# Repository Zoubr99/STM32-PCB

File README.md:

# STM32-PCB
 This Repo contains the KiCad 8.0 Files for an STM32-BLE Dev Board

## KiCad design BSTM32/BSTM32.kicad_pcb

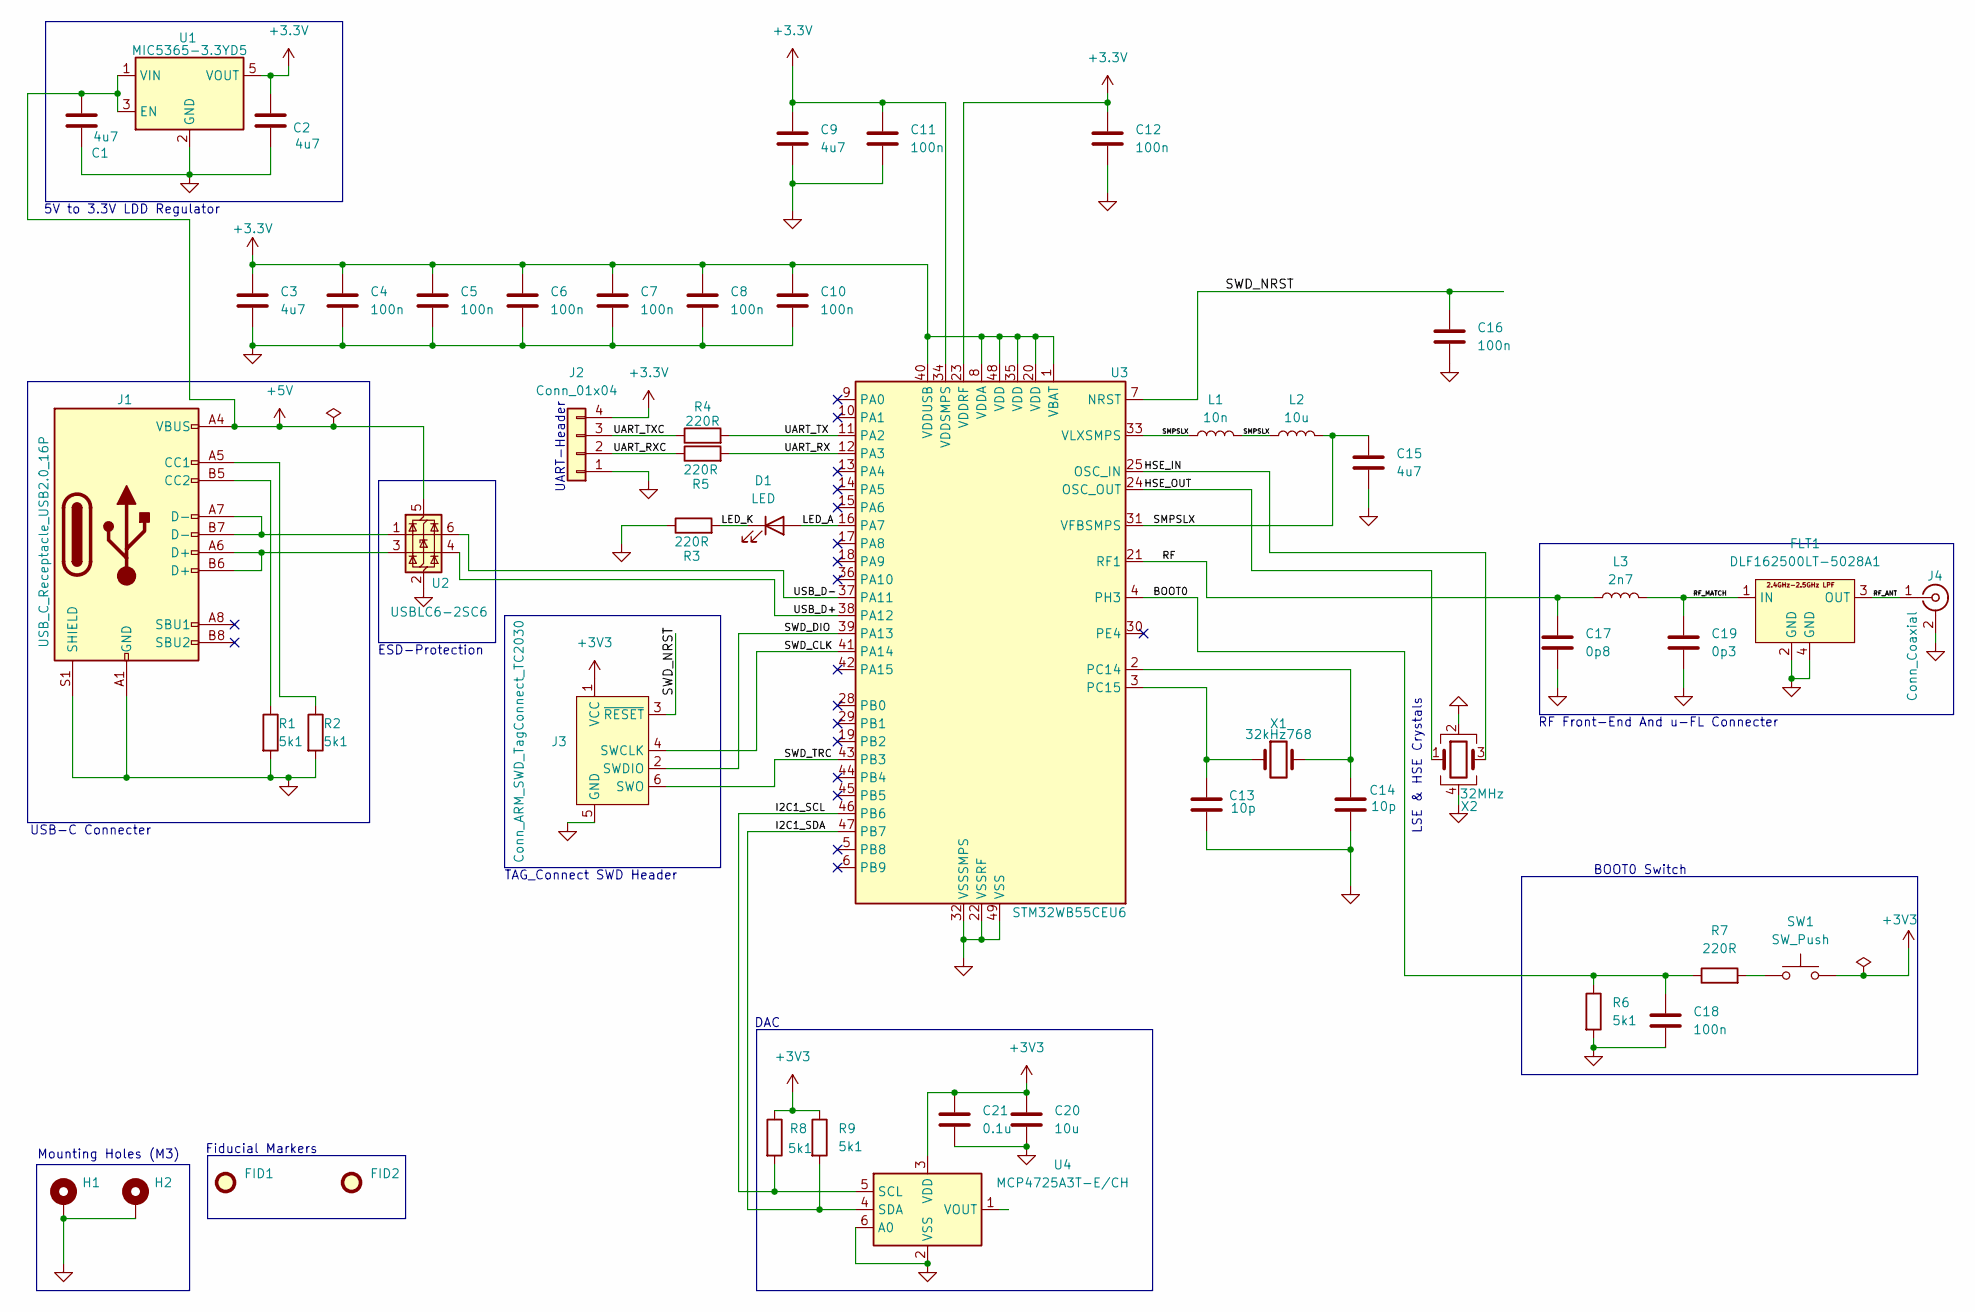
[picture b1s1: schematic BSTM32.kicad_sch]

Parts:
C1, C2, C3, C9, C15: 4u7; C_0603_1608Metric
C4, C5, C6, C7, C8, C10, C11, C12, C16, C18: 100n; C_0402_1005Metric
C13, C14: 10p; C_0402_1005Metric
C17: 0p8; C_0402_1005Metric
C19: 0p3; C_0402_1005Metric
C20: 10u; C_0805_2012Metric
C21: 0.1u; C_01005_0402Metric
D1: LED; LED_0402_1005Metric
FID1, FID2: Fiducial; Fiducial_1mm_Mask2mm
FLT1: DLF162500LT-5028A1
H1, H2: MountingHole_Pad; MountingHole_2.2mm_M2_Pad
J1: USB_C_Receptacle_USB2.0_16P; USB_C_Receptacle_GCT_USB4105-xx-A_16P_TopMnt_Horizontal
J2: Conn_01x04; Molex_PicoBlade_53048-0410_1x04_P1.25mm_Horizontal
J3: Conn_ARM_SWD_TagConnect_TC2030; Tag-Connect_TC2030-IDC-FP_2x03_P1.27mm_Vertical
J4: Conn_Coaxial; U.FL_Hirose_U.FL-R-SMT-1_Vertical
L1: 10n; L_0402_1005Metric
L2: 10u; L_0805_2012Metric
L3: 2n7; L_0402_1005Metric
R1, R2, R6, R8, R9: 5k1; R_0402_1005Metric
R3, R4, R5: 220R; R_0402_1005Metric
R7: 220R; C_0603_1608Metric
SW1: SW_Push; SW_SPST_CK_RS282G05A3
U1: MIC5365-3.3YD5; SOT-23-5
U2: USBLC6-2SC6; SOT-23-6
U3: STM32WB55CEU6; QFN-48-1EP_7x7mm_P0.5mm_EP5.6x5.6mm
U4: MCP4725A3T-E/CH; SOT-23-6
X1: 32kHz768; Crystal_SMD_2012-2Pin_2.0x1.2mm
X2: 32MHz; Crystal_SMD_2016-4Pin_2.0x1.6mm

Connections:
+3.3V: C2.1, C3.1, C4.1, C5.1, C6.1, C7.1, C8.1, C9.1, C10.1, C11.1, C12.1, J2.4, U1.5 (VOUT), U3.1 (VBAT), U3.8 (VDDA), U3.20 (VDD), U3.23 (VDDRF), U3.34 (VDDSMPS), U3.35 (VDD), U3.40 (VDDUSB), U3.48 (VDD)
+3V3: C20.1, C21.1, J3.1 (VCC), R8.1, R9.1, SW1.2, U4.3 (VDD)
+5V: C1.1, J1.A4 (VBUS), J1.A9 (VBUS), J1.B4 (VBUS), J1.B9 (VBUS), U1.1 (VIN), U1.3 (EN), U2.5 (VBUS)
/HSE_IN: U3.25 (OSC_IN), X2.3
/HSE_OUT: U3.24 (OSC_OUT), X2.1
/I2C1_SCL: R8.2, U3.46 (PB6), U4.5 (SCL)
/I2C1_SDA: R9.2, U3.47 (PB7), U4.4 (SDA)
/LED_A: D1.2 (A), U3.16 (PA7)
/LED_K: D1.1 (K), R3.2
/RF: C17.1, L3.1, U3.21 (RF1)
/RF_ANT: FLT1.3 (OUT), J4.1 (In)
/RF_MATCH: C19.1, FLT1.1 (IN), L3.2
/SMPSLX: C15.1, L1.1, L1.2, L2.1, L2.2, U3.31 (VFBSMPS), U3.33 (VLXSMPS)
/SWD_CLK: J3.4 (SWCLK), U3.41 (PA14)
/SWD_DIO: J3.2 (SWDIO), U3.39 (PA13)
/SWD_NRST: C16.1, J3.3 (~RESET), U3.7 (NRST)
/SWD_TRC: J3.6 (SWO), U3.43 (PB3)
/UART_RX: R5.2, U3.12 (PA3)
/UART_RXC: J2.2, R5.1
/UART_TX: R4.2, U3.11 (PA2)
/UART_TXC: J2.3, R4.1
/USB_D+: U2.4 (I/O2), U3.38 (PA12)
/USB_D-: U2.6 (I/O1), U3.37 (PA11)
GND: C1.2, C2.2, C3.2, C4.2, C5.2, C6.2, C7.2, C8.2, C9.2, C10.2, C11.2, C12.2, C13.2, C14.2, C15.2, C16.2, C17.2, C18.2, C19.2, C20.2, C21.2, FLT1.2 (GND), FLT1.4 (GND), H1.1, H2.1, J1.A1 (GND), J1.A12 (GND), J1.B1 (GND), J1.B12 (GND), J1.S1 (SHIELD), J2.1, J3.5 (GND), J4.2 (Ext), R1.2, R2.2, R3.1, R6.2, U1.2 (GND), U2.2 (GND), U3.22 (VSSRF), U3.32 (VSSSMPS), U3.49 (VSS), U4.2 (VSS), U4.6 (A0), X2.2, X2.4
unnamed: J1.A5 (CC1), R2.1
unnamed: J1.B5 (CC2), R1.1
unnamed: J1.A6 (D+), J1.B6 (D+), U2.3 (I/O2)
unnamed: J1.A7 (D-), J1.B7 (D-), U2.1 (I/O1)
unnamed: R7.2, SW1.1
unnamed: C14.1, U3.2 (PC14), X1.2
unnamed: C13.1, U3.3 (PC15), X1.1
unnamed: C18.1, R6.1, R7.1, U3.4 (PH3)

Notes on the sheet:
RF Front-End And u-FL Connecter
ESD-Protection
Mounting Holes (M3)
LSE & HSE Crystals
Fiducial Markers
USB-C Connecter
UART-Header
TAG_Connect SWD Header
5V to 3.3V LDD Regulator
BOOT0 Switch
DAC

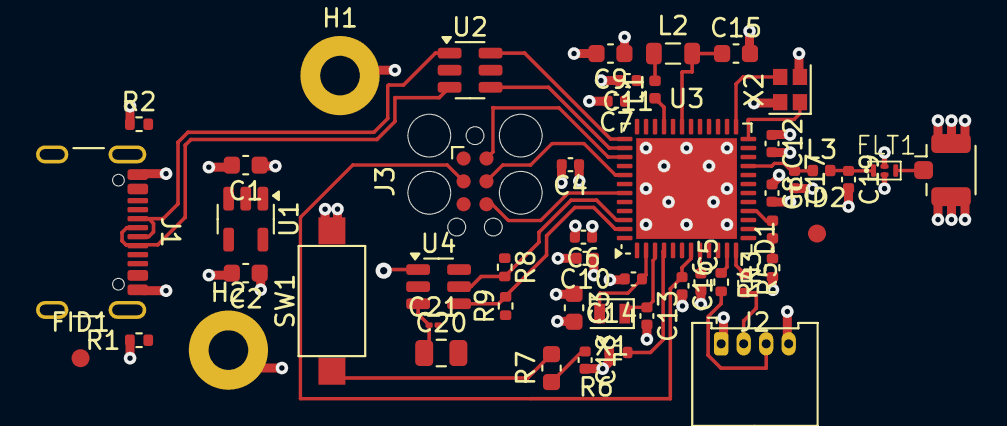
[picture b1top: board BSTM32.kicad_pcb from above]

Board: 4 copper layers, 50 parts (0 on the bottom side), 32 nets.

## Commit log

2024-11-16 publishing the codes
